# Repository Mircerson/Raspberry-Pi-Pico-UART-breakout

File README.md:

# Raspberry Pi Pico UART breakout
 A simple 2-layer PCB making the Raspberry Pi Pico a 6 way UART adapter.
 The main purpose of this board is to be the programmer for the AERQ project which uses UART 0 to pass LoRa credentials and other settings to the system.
<figure>

<figcaption>Figure 1: 3D simulation of the front of the board</figcaption>
</figure>

<figure>

<figcaption>Figure 2: 3D simulation of the back of the board</figcaption>
</figure>

# Hardware
The board uses  2.54mm holes for the UART ports and a resistor/LED to indicate the 3v3 bus. 

The board dimensions are: 44.75mm x 55mm 

### Why the curved traces?
No reason in particular, it was a test for [easyw's](https://github.com/easyw/RF-tools-KiCAD) plugin.

<figure>

<figcaption>Figure 3: Layout</figcaption>
</figure>

# Software
To make use of all the 6 UART ports available, use [harrywalsh's](https://github.com/harrywalsh/pico-hw_and_pio-uart-gridge/tree/HW_and_pio_uarts) software.

This will make the Pi Pico into a 6 way UART adapter, all the UART ports are marked on the board.

# Limits
<b>The maximum output on the 3v3 rail should not exceed ~ 300 mA.</b>

# License
This PCB uses [ncarandini's](https://github.com/ncarandini/KiCad-RP-Pico) footprint for the Raspberry Pi Pico.

# Disclaimer
This project/hardware is provided without warranty, according to the MIT License, and should therefore not be used where it may endanger life, financial stakes, or cause discomfort and inconvenience to others.

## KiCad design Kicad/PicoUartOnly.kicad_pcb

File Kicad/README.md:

# Raspberry Pi Pico UART breakout

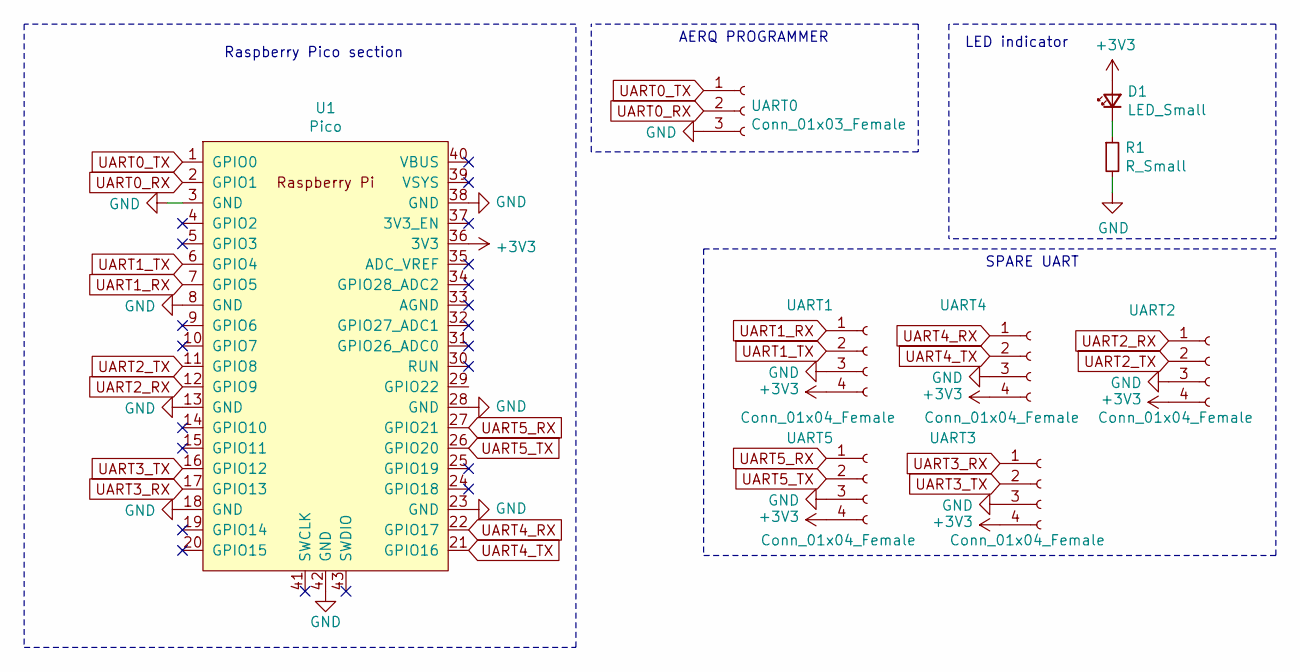
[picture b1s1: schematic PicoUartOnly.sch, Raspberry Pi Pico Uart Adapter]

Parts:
D1: LED_Small; LED_D5.0mm_Horizontal_O3.81mm_Z3.0mm
R1: R_Small; R_Axial_DIN0207_L6.3mm_D2.5mm_P2.54mm_Vertical
U1: Pico; RPi_Pico_SMD_TH
UART0: Conn_01x03_Female; PinSocket_1x03_P2.54mm_Vertical
UART1, UART2, UART3, UART4, UART5: Conn_01x04_Female; PinSocket_1x04_P2.54mm_Vertical

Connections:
+3V3: D1.2 (A), U1.36 (3V3), UART1.4, UART2.4, UART3.4, UART4.4, UART5.4
GND: R1.2, U1.3 (GND), U1.8 (GND), U1.13 (GND), U1.18 (GND), U1.23 (GND), U1.28 (GND), U1.38 (GND), U1.42 (GND), UART0.3, UART1.3, UART2.3, UART3.3, UART4.3, UART5.3
unnamed: D1.1 (K), R1.1
UART0_RX: U1.2 (GPIO1), UART0.2
UART0_TX: U1.1 (GPIO0), UART0.1
UART1_RX: U1.7 (GPIO5), UART1.1
UART1_TX: U1.6 (GPIO4), UART1.2
UART2_RX: U1.12 (GPIO9), UART2.1
UART2_TX: U1.11 (GPIO8), UART2.2
UART3_RX: U1.17 (GPIO13), UART3.1
UART3_TX: U1.16 (GPIO12), UART3.2
UART4_RX: U1.22 (GPIO17), UART4.1
UART4_TX: U1.21 (GPIO16), UART4.2
UART5_RX: U1.27 (GPIO21), UART5.1
UART5_TX: U1.26 (GPIO20), UART5.2

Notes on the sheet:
AERQ PROGRAMMER
Raspberry Pico section
LED indicator
SPARE UART

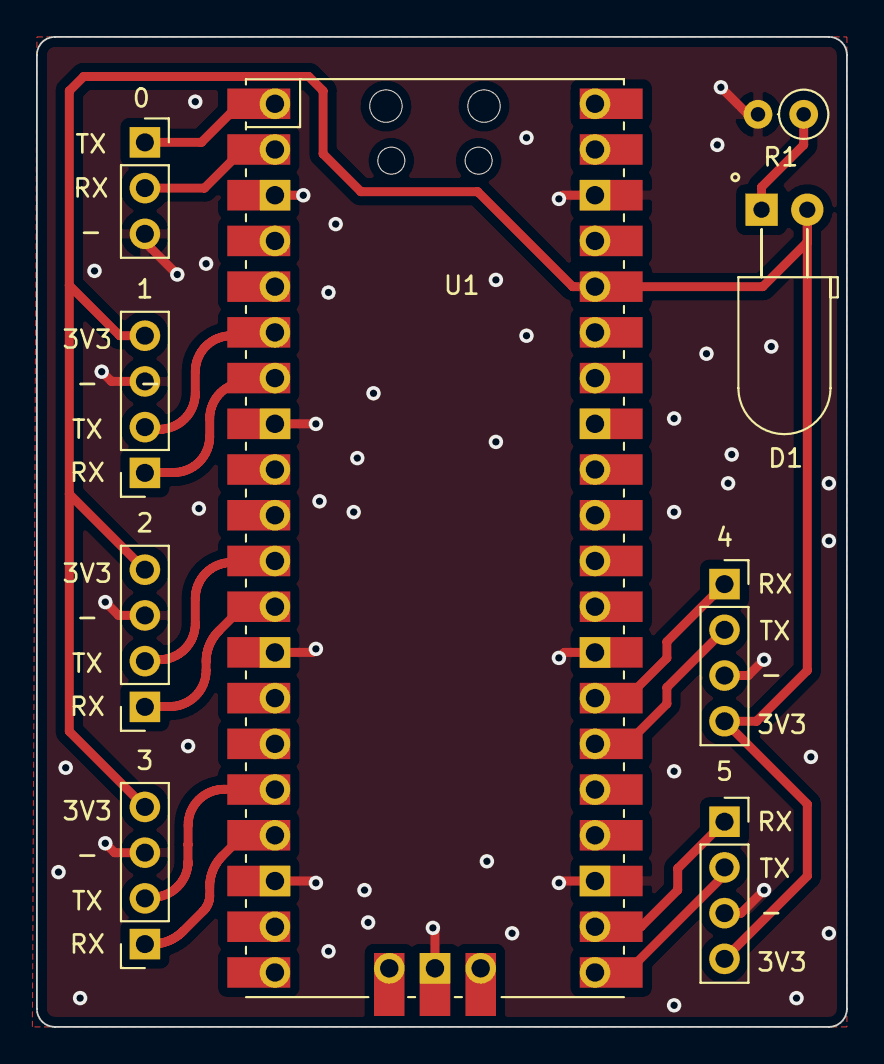
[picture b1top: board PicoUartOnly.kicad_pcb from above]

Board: 2 copper layers, 45.0 x 55.0 mm, 9 parts (0 on the bottom side), 15 nets.

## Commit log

2022-03-21 Publish
2022-03-21 Update README.md
    Test center
2022-03-21 Updated readme md
2022-03-21 Final
